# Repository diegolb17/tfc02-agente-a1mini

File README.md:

# Sistema mecatrónico con agente de IA para la supervisión y remoción de piezas en la Bambu Lab A1 mini

Repositorio de la tesis de Diego Manuel Luna Baldwin (PUCP, Ingeniería Mecatrónica, 1MTR02 Trabajo de Fin de Carrera 2, 2026-2). Asesor: Christihan Laurel Bravo.

Contiene el código de la implementación parcial del dominio de software y los guiones que generan los cálculos, los planos, el proyecto electrónico y los diagramas de la tesis. El texto de la tesis no forma parte del repositorio.

## Estructura

| Carpeta | Contenido |
|---|---|
| `implementacion/` | Orquestador en Python: bot de Telegram, cliente MQTT de la impresora, cámara integrada de la A1 mini, servidor MCP con las nueve funciones del agente, agente con GPT-5.4 mini, registro SQLite con envío al panel y pruebas |
| `implementacion/panel/` | Página de administración en Cloudflare Workers con D1 y R2: esquema de la base de datos (Tabla 22 de la tesis), páginas de la Tabla 23 y sincronización con el orquestador |
| `calculos/` | Guiones de las memorias de cálculo (enfriamiento, vuelco, costos, potencia) y sus resultados en JSON |
| `planos/` | Generadores de las láminas mecánicas y eléctricas con un motor de dibujo propio (`motor/`) y los guiones de exportación desde Fusion 360 (`fusion/`) |
| `electronica/` | Guiones que generan el esquemático y la placa en KiCad, y el proyecto `TFC_Remocion` con su verificación eléctrica y de reglas de diseño |
| `diagramas/` | Fuentes TikZ de los diagramas de estados, de flujo y de comunicaciones del capítulo 5 |
| `armar_repositorio.py` | Vuelve a armar este repositorio desde las carpetas de trabajo y escanea secretos antes de cada subida |

## Implementación parcial

Requisitos: Python 3.11 o posterior.

```
cd implementacion
python -m pip install -r requisitos.txt
copy .env.ejemplo .env      (y completa los valores)
```

Modos de ejecución:

| Orden | Qué hace |
|---|---|
| `python -m orquestador --simular --consola` | Todo simulado y en consola; no usa red ni claves |
| `python -m orquestador --simular --registrar-operador` | Bot real de Telegram con impresora, cámara y modelo simulados; el primer `/start` privado queda como operador autorizado. En este modo `/simular_impresion` y `/simular_falla` recorren el ciclo completo |
| `python -m orquestador --simular-modelo` | Impresora y cámara reales; el modelo responde con veredictos fijos, sin costo |
| `python -m orquestador` | Sistema real: requiere la impresora en modo LAN y modo desarrollador y la variable `OPENAI_API_KEY` |
| `python -m orquestador.servidor_funciones` | Lanza solo el servidor MCP por stdio, con impresora simulada, para inspeccionar sus funciones |
| `python pruebas/prueba_simulacion.py` | Prueba de punta a punta en cuatro escenarios; deja la salida en `pruebas/salida_simulacion.txt` |
| `python pruebas/prueba_modelo_real.py` | 20 consultas reales a GPT-5.4 mini con las imágenes de prueba: tokens, latencia y costo en `pruebas/salida_modelo_real.txt` |
| `python pruebas/poblar_panel.py` | Envía al panel tres ciclos simulados completos |
| `python pruebas/capturas_panel.py` | Capturas de pantalla de cada página del panel con Edge sin interfaz (Playwright) |
| `python pruebas/demo_telegram.py` | Conversación tipo hacia el chat del operador, con impresora simulada |

Criterios que el código aplica, tomados del capítulo 5 de la tesis:

- El agente solo actúa a través de las nueve funciones del servidor MCP. Ninguna mueve ejes ni cambia temperaturas, y las que tienen efecto físico comprueban su restricción antes de ejecutarse.
- La decisión sobre la confianza la toma el orquestador, no el modelo. Con el umbral al máximo (1.0), que es el valor inicial mientras no se calibre con un conjunto de prueba, el sistema pide siempre la confirmación del operador.
- La supervisión captura cada 10 minutos a 800 por 600 píxeles. Una posible falla se confirma con una segunda consulta a resolución completa antes de pausar la impresora.
- El bot atiende solo al identificador del operador autorizado. Las órdenes de rutina se reconocen por palabras clave sin llamar al modelo.
- En esta implementación, la imagen sale de la cámara integrada de la A1 mini (puerto 6000) en lugar de la ESP32-CAM del diseño. El microcontrolador de la secuencia de remoción está simulado con los mismos tiempos máximos.

## Panel de administración

```
cd implementacion/panel
npx wrangler d1 create tfc02-panel-db          (y copia su identificador en wrangler.toml)
npx wrangler r2 bucket create tfc02-panel-capturas
npx wrangler d1 execute tfc02-panel-db --remote --file=schema.sql
npx wrangler deploy
npx wrangler secret put ADMIN_USUARIO          (y ADMIN_HASH, SESION_CLAVE, EQUIPO_CLAVE)
```

`ADMIN_HASH` tiene la forma `pbkdf2_sha256$100000$sal$resumen` (Base64) y se calcula fuera del worker: la contraseña nunca se guarda en claro. `EQUIPO_CLAVE` es el mismo valor que `PANEL_CLAVE` en el `.env` del orquestador, que envía sus filas pendientes cada 30 s y marca como pendiente lo que no pudo subir.

## Guiones de cálculo, planos y electrónica

- Los guiones de `calculos/` reproducen las cifras de los Anexos E y F; cada uno escribe su JSON de resultados.
- Los generadores de `planos/` leen la geometría que exporta `fusion/_exportar_geometria.py` desde el modelo de Fusion 360. Esa geometría (unos 70 MB) no se incluye.
- En `electronica/`, la cadena es `generar_esquematico.py`, `exportar.py`, `clases_de_red.py`, `generar_placa.py`, `rutear.py` y `vias_costura.py`. Las tres últimas se ejecutan con el Python de KiCad.

## Lo que no está

El texto y los PDF de la tesis, la geometría exportada de Fusion 360 y cualquier clave o token. Los secretos van en `implementacion/.env`, que está excluido del control de versiones.

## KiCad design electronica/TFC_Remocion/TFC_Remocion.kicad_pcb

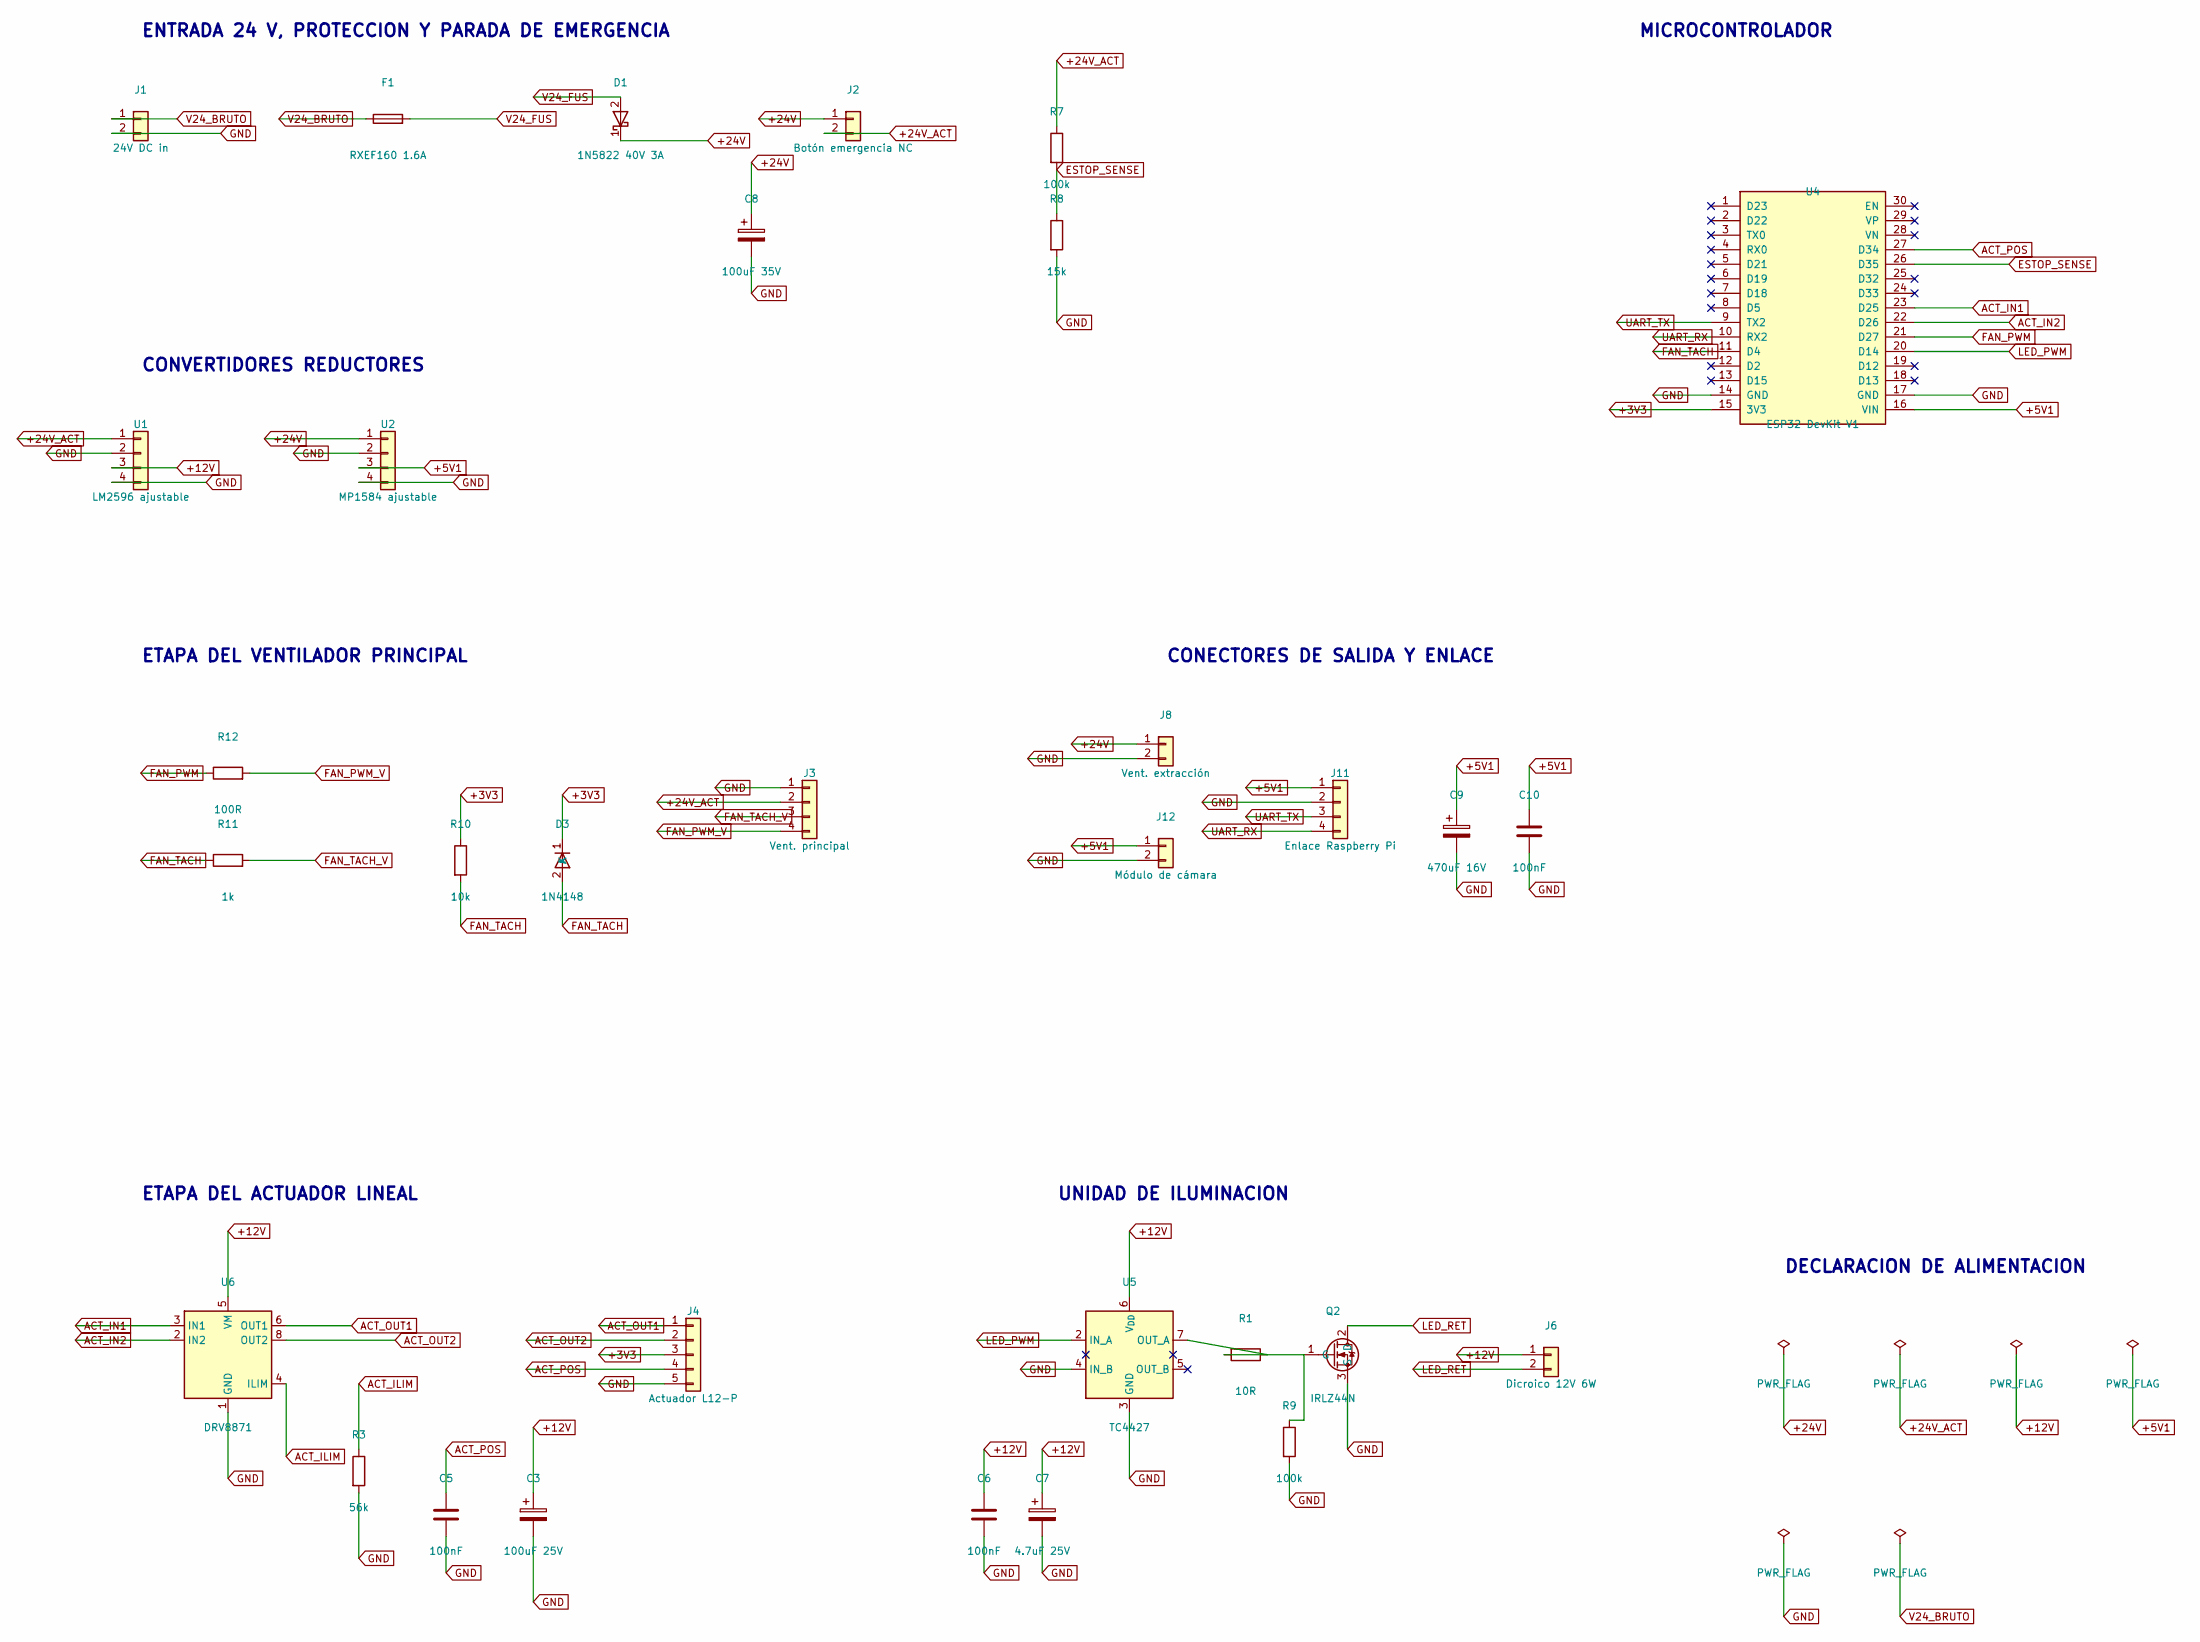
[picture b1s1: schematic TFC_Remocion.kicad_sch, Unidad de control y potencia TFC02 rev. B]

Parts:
C3: 100uF 25V; CP_Radial_D8.0mm_P3.50mm
C5, C6, C10: 100nF; C_Disc_D5.0mm_W2.5mm_P5.00mm
C7: 4.7uF 25V; CP_Radial_D5.0mm_P2.00mm
C8: 100uF 35V; CP_Radial_D8.0mm_P3.50mm
C9: 470uF 16V; CP_Radial_D8.0mm_P3.50mm
D1: 1N5822 40V 3A; D_DO-201AD_P15.24mm_Horizontal
D3: 1N4148; D_DO-35_SOD27_P7.62mm_Horizontal
F1: RXEF160 1.6A; Fuse_Bourns_MF-RG300
J1: 24V DC in; PinHeader_1x02_P2.54mm_Vertical
J2: Botón emergencia NC; PinHeader_1x02_P2.54mm_Vertical
J3: Vent. principal; PinHeader_1x04_P2.54mm_Vertical
J4: Actuador L12-P; PinHeader_1x05_P2.54mm_Vertical
J6: Dicroico 12V 6W; PinHeader_1x02_P2.54mm_Vertical
J8: Vent. extracción; PinHeader_1x02_P2.54mm_Vertical
J11: Enlace Raspberry Pi; PinHeader_1x04_P2.54mm_Vertical
J12: Módulo de cámara; PinHeader_1x02_P2.54mm_Vertical
Q2: IRLZ44N; TO-220-3_Vertical
R1: 10R; R_Axial_DIN0207_L6.3mm_D2.5mm_P10.16mm_Horizontal
R3: 56k; R_Axial_DIN0207_L6.3mm_D2.5mm_P10.16mm_Horizontal
R7, R9: 100k; R_Axial_DIN0207_L6.3mm_D2.5mm_P10.16mm_Horizontal
R8: 15k; R_Axial_DIN0207_L6.3mm_D2.5mm_P10.16mm_Horizontal
R10: 10k; R_Axial_DIN0207_L6.3mm_D2.5mm_P10.16mm_Horizontal
R11: 1k; R_Axial_DIN0207_L6.3mm_D2.5mm_P10.16mm_Horizontal
R12: 100R; R_Axial_DIN0207_L6.3mm_D2.5mm_P10.16mm_Horizontal
U1: LM2596 ajustable; PinHeader_1x04_P2.54mm_Vertical
U2: MP1584 ajustable; PinHeader_1x04_P2.54mm_Vertical
U4: ESP32 DevKit V1; ESP32_DevKitV1_30pin
U5: TC4427; DIP-8_W7.62mm
U6: DRV8871; PinHeader_1x08_P2.54mm_Vertical

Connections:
+3V3: D3.1 (K), J4.3, R10.1, U4.15 (3V3)
+5V1: C9.1, C10.1, J11.1, J12.1, U2.3, U4.16 (VIN)
+12V: C3.1, C6.1, C7.1, J6.1, U1.3, U5.6 (V_{DD}), U6.5 (VM)
+24V: C8.1, D1.1 (K), J2.1, J8.1, U2.1
+24V_ACT: J2.2, J3.2, R7.1, U1.1
ACT_ILIM: R3.1, U6.4 (ILIM)
ACT_IN1: U4.23 (D25), U6.3 (IN1)
ACT_IN2: U4.22 (D26), U6.2 (IN2)
ACT_OUT1: J4.1, U6.6 (OUT1)
ACT_OUT2: J4.2, U6.8 (OUT2)
ACT_POS: C5.1, J4.4, U4.27 (D34)
ESTOP_SENSE: R7.2, R8.1, U4.26 (D35)
FAN_PWM: R12.1, U4.21 (D27)
FAN_PWM_V: J3.4, R12.2
FAN_TACH: D3.2 (A), R10.2, R11.1, U4.11 (D4)
FAN_TACH_V: J3.3, R11.2
GND: C3.2, C5.2, C6.2, C7.2, C8.2, C9.2, C10.2, J1.2, J3.1, J4.5, J8.2, J11.2, J12.2, Q2.3 (S), R3.2, R8.2, R9.2, U1.2, U1.4, U2.2, U2.4, U4.14 (GND), U4.17 (GND), U5.3 (GND), U5.4 (IN_B), U6.1 (GND), U6.7 (GND), U6.9 (GND)
LED_PWM: U4.20 (D14), U5.2 (IN_A)
LED_RET: J6.2, Q2.2 (D)
unnamed: Q2.1 (G), R1.2, R9.1
unnamed: R1.1, U5.7 (OUT_A)
UART_RX: J11.4, U4.10 (RX2)
UART_TX: J11.3, U4.9 (TX2)
V24_BRUTO: F1.1, J1.1
V24_FUS: D1.2 (A), F1.2

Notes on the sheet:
ENTRADA 24 V, PROTECCION Y PARADA DE EMERGENCIA
CONVERTIDORES REDUCTORES
ETAPA DEL VENTILADOR PRINCIPAL
ETAPA DEL ACTUADOR LINEAL
UNIDAD DE ILUMINACION
MICROCONTROLADOR
CONECTORES DE SALIDA Y ENLACE
DECLARACION DE ALIMENTACION

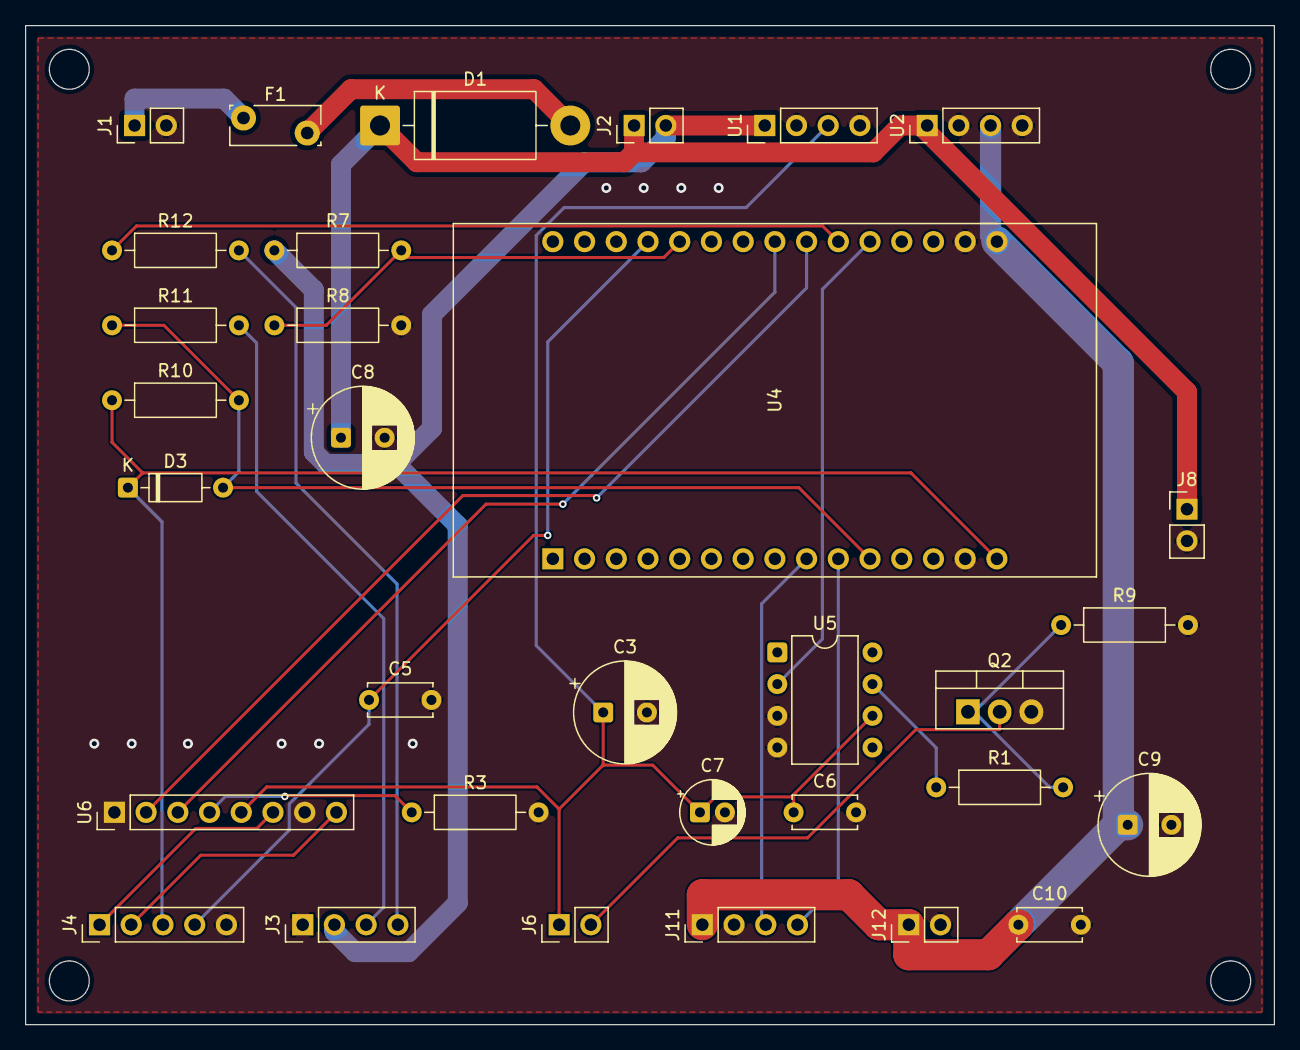
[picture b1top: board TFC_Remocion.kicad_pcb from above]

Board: 2 copper layers, 100.0 x 80.0 mm, 32 parts (0 on the bottom side), 25 nets.

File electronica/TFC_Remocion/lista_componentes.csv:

"Reference","Value","Footprint","Nota"
"C3","100uF 25V","Capacitor_THT:CP_Radial_D8.0mm_P3.50mm",""
"C5,C6,C10","100nF","Capacitor_THT:C_Disc_D5.0mm_W2.5mm_P5.00mm",""
"C7","4.7uF 25V","Capacitor_THT:CP_Radial_D5.0mm_P2.00mm",""
"C8","100uF 35V","Capacitor_THT:CP_Radial_D8.0mm_P3.50mm",""
"C9","470uF 16V","Capacitor_THT:CP_Radial_D8.0mm_P3.50mm",""
"D1","1N5822  40V 3A","Diode_THT:D_DO-201AD_P15.24mm_Horizontal",""
"D3","1N4148","Diode_THT:D_DO-35_SOD27_P7.62mm_Horizontal",""
"F1","RXEF160  1.6A","Fuse:Fuse_Bourns_MF-RG300","rearmable, 1.6 A de retención y 3.2 de disparo"
"J1","24V DC in","Connector_PinHeader_2.54mm:PinHeader_1x02_P2.54mm_Vertical","desde LRS-50-24"
"J2","Botón emergencia NC","Connector_PinHeader_2.54mm:PinHeader_1x02_P2.54mm_Vertical","ISO 13850, apertura positiva"
"J3","Vent. principal","Connector_PinHeader_2.54mm:PinHeader_1x04_P2.54mm_Vertical",""
"J4","Actuador L12-P","Connector_PinHeader_2.54mm:PinHeader_1x05_P2.54mm_Vertical",""
"J6","Dicroico 12V 6W","Connector_PinHeader_2.54mm:PinHeader_1x02_P2.54mm_Vertical",""
"J8","Vent. extracción","Connector_PinHeader_2.54mm:PinHeader_1x02_P2.54mm_Vertical",""
"J11","Enlace Raspberry Pi","Connector_PinHeader_2.54mm:PinHeader_1x04_P2.54mm_Vertical",""
"J12","Módulo de cámara","Connector_PinHeader_2.54mm:PinHeader_1x02_P2.54mm_Vertical",""
"Q2","IRLZ44N","Package_TO_SOT_THT:TO-220-3_Vertical",""
"R1","10R","Resistor_THT:R_Axial_DIN0207_L6.3mm_D2.5mm_P10.16mm_Horizontal",""
"R3","56k","Resistor_THT:R_Axial_DIN0207_L6.3mm_D2.5mm_P10.16mm_Horizontal","fija 1.14 A, no garantiza tope de fuerza"
"R7,R9","100k","Resistor_THT:R_Axial_DIN0207_L6.3mm_D2.5mm_P10.16mm_Horizontal",""
"R8","15k","Resistor_THT:R_Axial_DIN0207_L6.3mm_D2.5mm_P10.16mm_Horizontal",""
"R10","10k","Resistor_THT:R_Axial_DIN0207_L6.3mm_D2.5mm_P10.16mm_Horizontal",""
"R11","1k","Resistor_THT:R_Axial_DIN0207_L6.3mm_D2.5mm_P10.16mm_Horizontal",""
"R12","100R","Resistor_THT:R_Axial_DIN0207_L6.3mm_D2.5mm_P10.16mm_Horizontal",""
"U1","LM2596 ajustable","Connector_PinHeader_2.54mm:PinHeader_1x04_P2.54mm_Vertical","módulo, no componente discreto"
"U2","MP1584 ajustable","Connector_PinHeader_2.54mm:PinHeader_1x04_P2.54mm_Vertical","módulo, no componente discreto"
"U4","ESP32 DevKit V1","TFC:ESP32_DevKitV1_30pin","placa de 30 contactos, no el módulo suelto"
"U5","TC4427","Package_DIP:DIP-8_W7.62mm",""
"U6","DRV8871","Connector_PinHeader_2.54mm:PinHeader_1x08_P2.54mm_Vertical","módulo de ruptura sobre tira de contactos"
